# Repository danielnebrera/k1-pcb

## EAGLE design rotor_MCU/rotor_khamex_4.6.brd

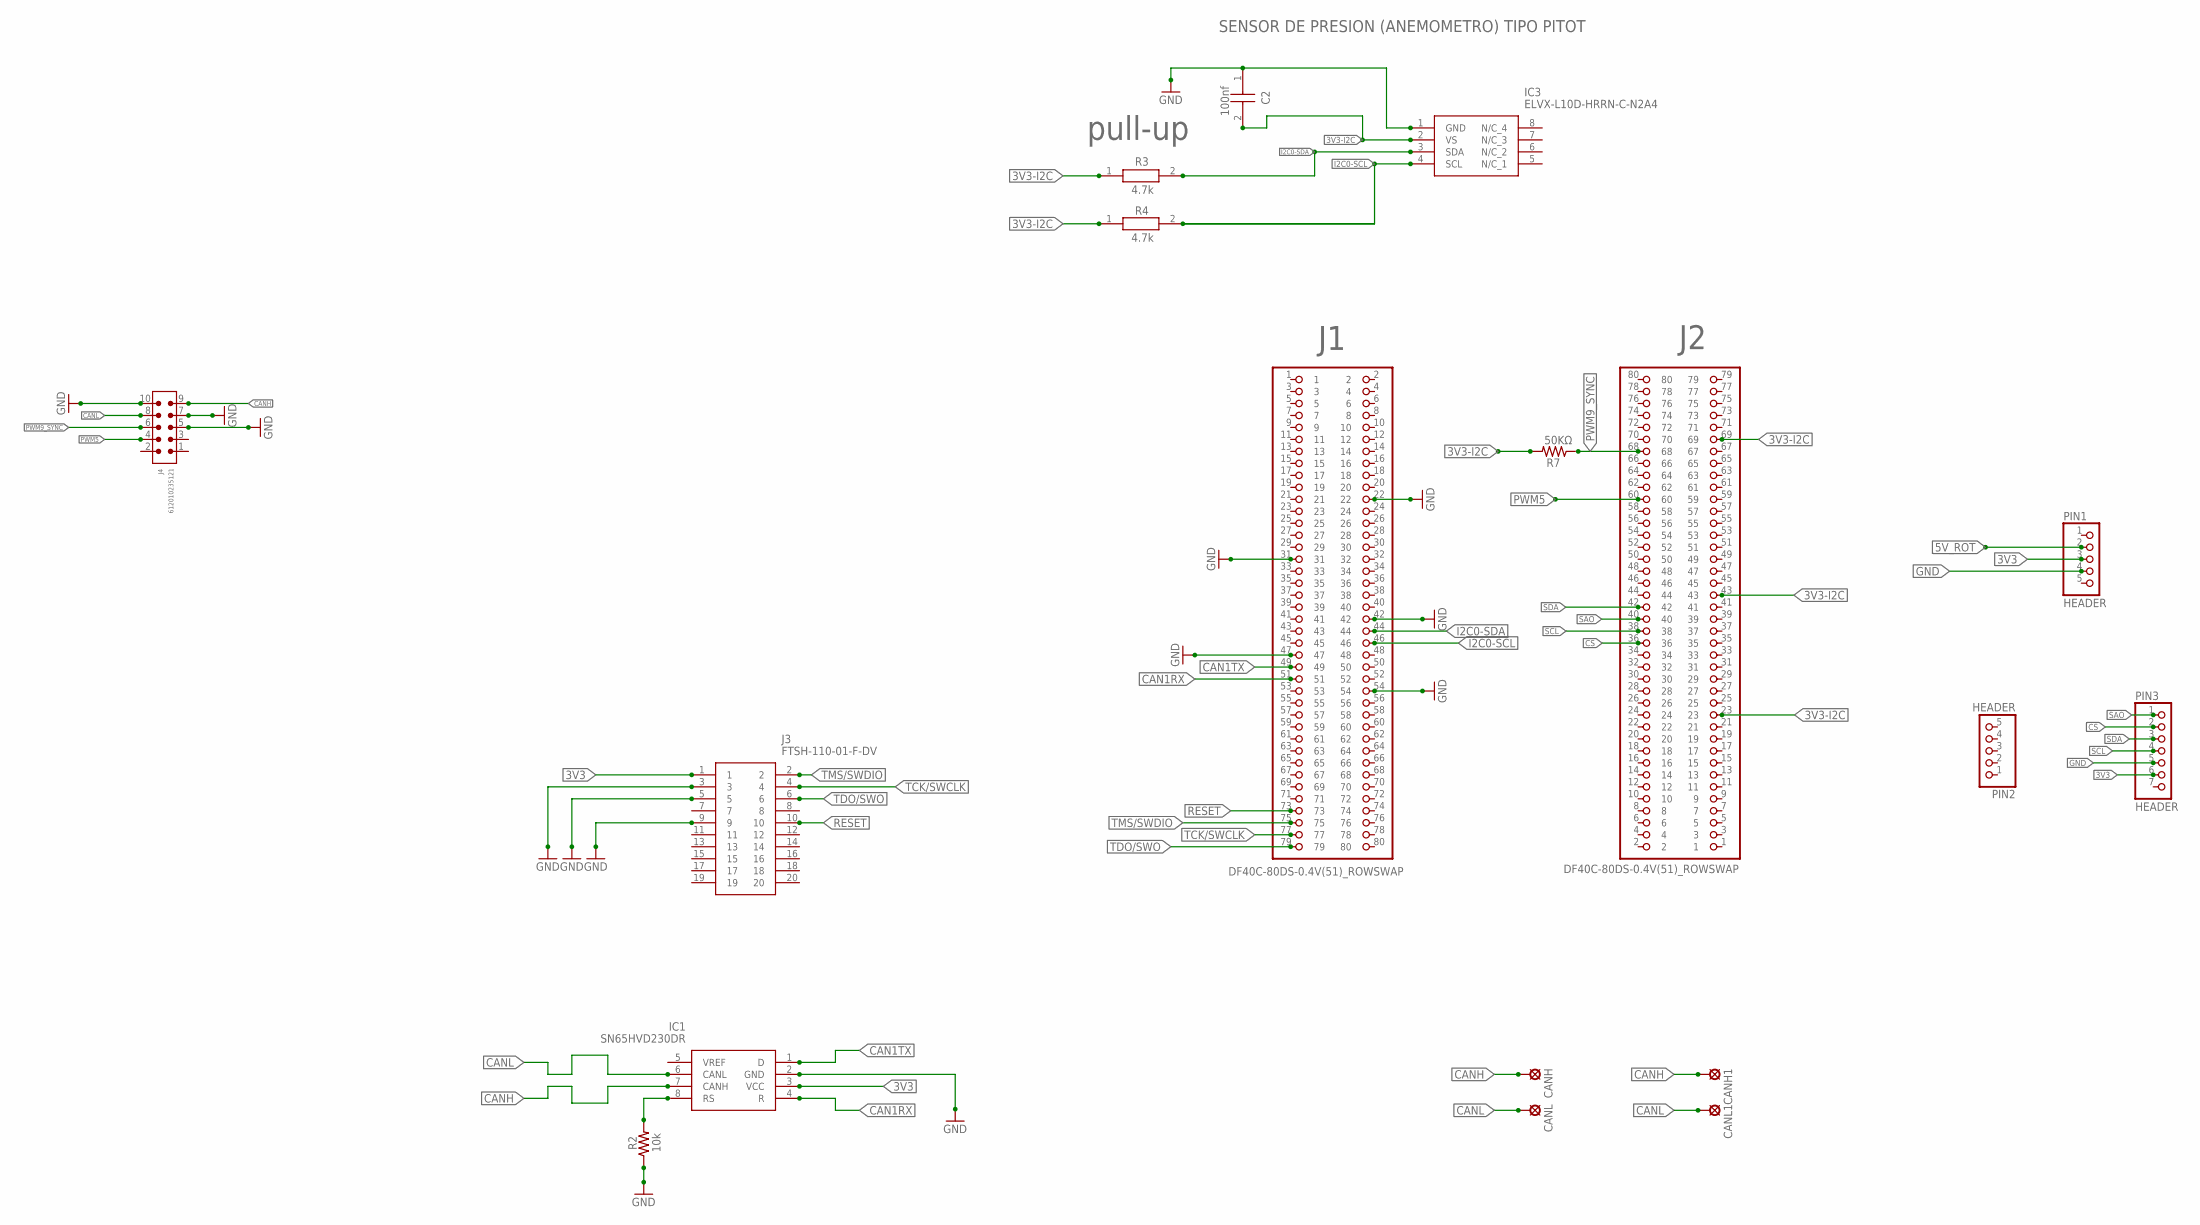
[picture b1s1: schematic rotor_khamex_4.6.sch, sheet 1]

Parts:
C2: 100nf; CAPC2012X145N
CANH, CANH1: LSP11
CANL, CANL1: LSP11
IC1: SN65HVD230DR; SOT127P600X175-8N
IC3: ELVX-L10D-HRRN-C-N2A4; ELVXL10DHRRNCN2A4
J1, J2: DF40C-80DS-0.4V(51)_ROWSWAP; HRS_DF40C-80DS-0.4V(51)_ROWSWAP
J3: FTSH-110-01-F-DV; FTSH-110-XX-YYY-DV
J4: 612010235121
PIN1, PIN2: HEADER; 1X05
PIN3: HEADER; 1X07
R2: 10k; M0805
R3, R4: 4.7k; RESC2012X50N
R7: 50KΩ; M0805

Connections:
3V3: IC1.3 (VCC), J3.1, PIN1.3, PIN3.6
3V3-I2C: C2.2, IC3.2 (VS), J2.23, J2.43, J2.69, R3.1, R4.1, R7.2
5V_ROT: PIN1.2; also elsewhere on the board
CAN1RX: IC1.4 (R), J1.51
CAN1TX: IC1.1 (D), J1.49
CANH: CANH.MP, CANH1.MP, IC1.7 (CANH), J4.9
CANL: CANL.MP, CANL1.MP, IC1.6 (CANL), J4.8
CS: J2.36, PIN3.2
GND: C2.1, IC1.2 (GND), IC3.1 (GND), J1.22, J1.31, J1.42, J1.47, J1.54, J3.3, J3.5, J3.9, J4.5, J4.7, J4.10, PIN1.4, PIN3.5, R2.1; also elsewhere on the board
I2C0-SCL: IC3.4 (SCL), J1.46, R4.2
I2C0-SDA: IC3.3 (SDA), J1.44, R3.2
unnamed: IC1.8 (RS), R2.2
PWM5: J2.60, J4.4
PWM9_SYNC: J2.68, J4.6, R7.1
RESET: J1.73, J3.10
SAO: J2.40, PIN3.1
SCL: J2.38, PIN3.4
SDA: J2.42, PIN3.3
TCK/SWCLK: J1.77, J3.4
TDO/SWO: J1.79, J3.6
TMS/SWDIO: J1.75, J3.2

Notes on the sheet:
SENSOR DE PRESION (ANEMOMETRO) TIPO PITOT
4.7k
pull-up

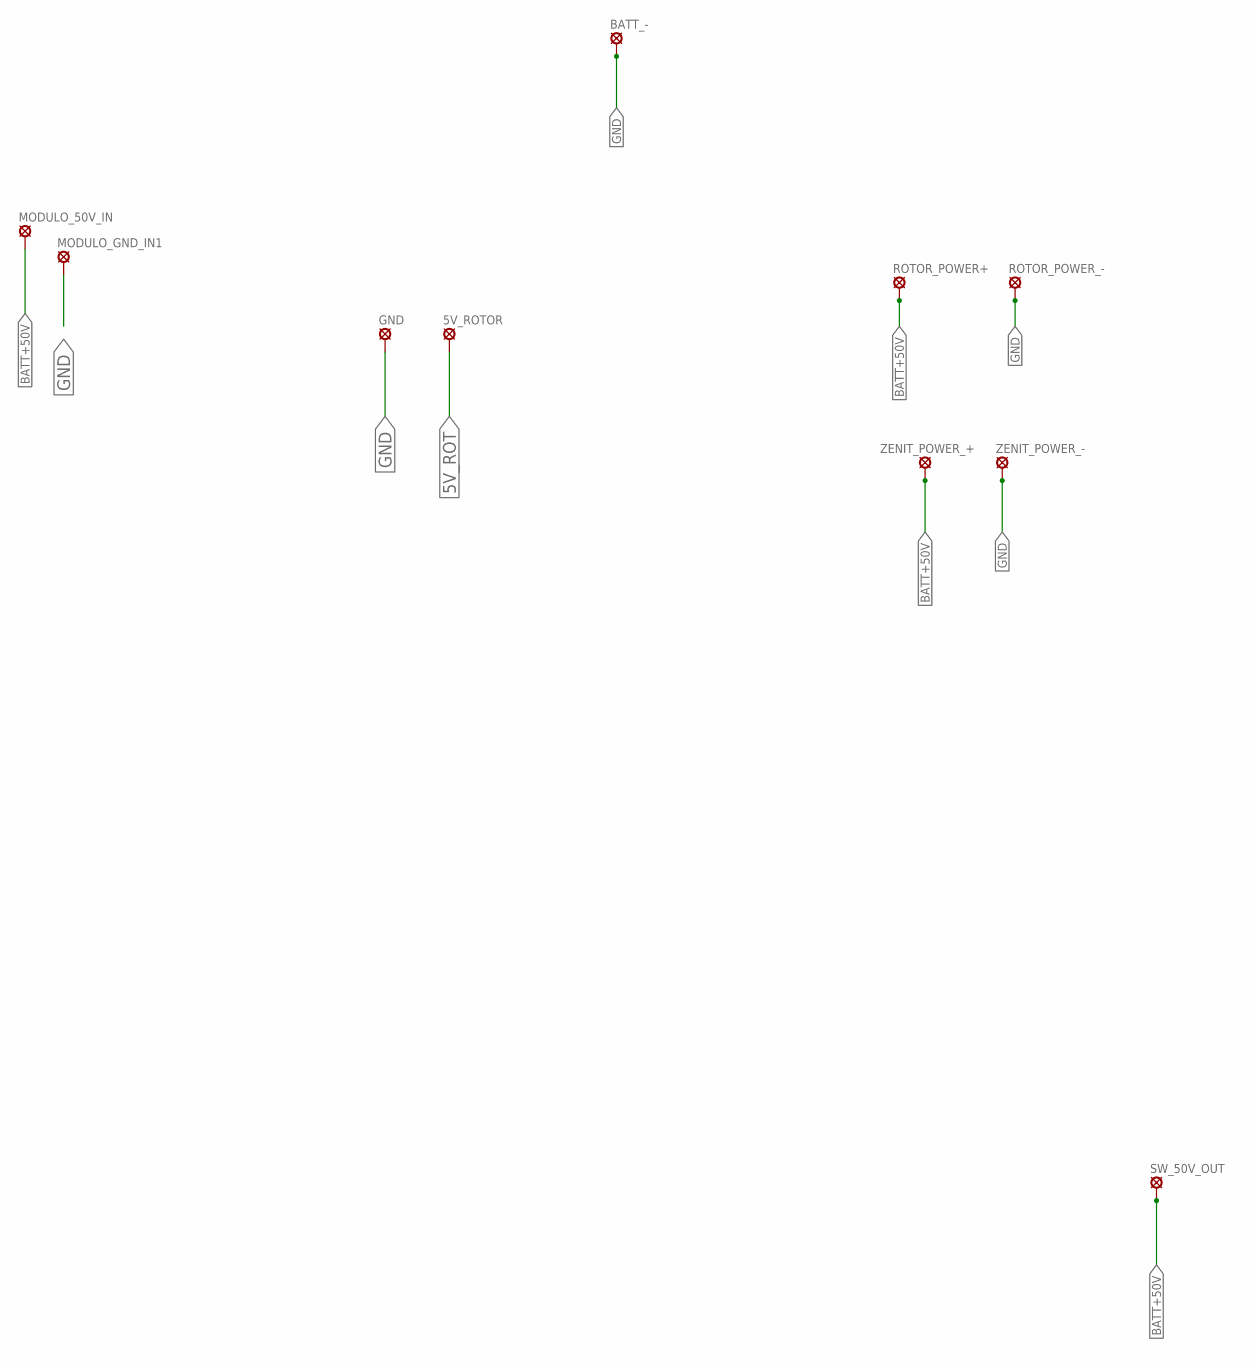
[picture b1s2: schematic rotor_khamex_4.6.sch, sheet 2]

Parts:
5V_ROTOR: SE14
BATT_-: SE14
GND: SE14
MODULO_50V_IN: SE14
MODULO_GND_IN1: SE14
ROTOR_POWER+: SE14
ROTOR_POWER_-: SE14
SW_50V_OUT: SE14
ZENIT_POWER_+: SE14
ZENIT_POWER_-: SE14

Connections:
5V_ROT: 5V_ROTOR.MP; also elsewhere on the board
BATT+50V: MODULO_50V_IN.MP, ROTOR_POWER+.MP, SW_50V_OUT.MP, ZENIT_POWER_+.MP
GND: BATT_-.MP, GND.MP, MODULO_GND_IN1.MP, ROTOR_POWER_-.MP, ZENIT_POWER_-.MP; also elsewhere on the board

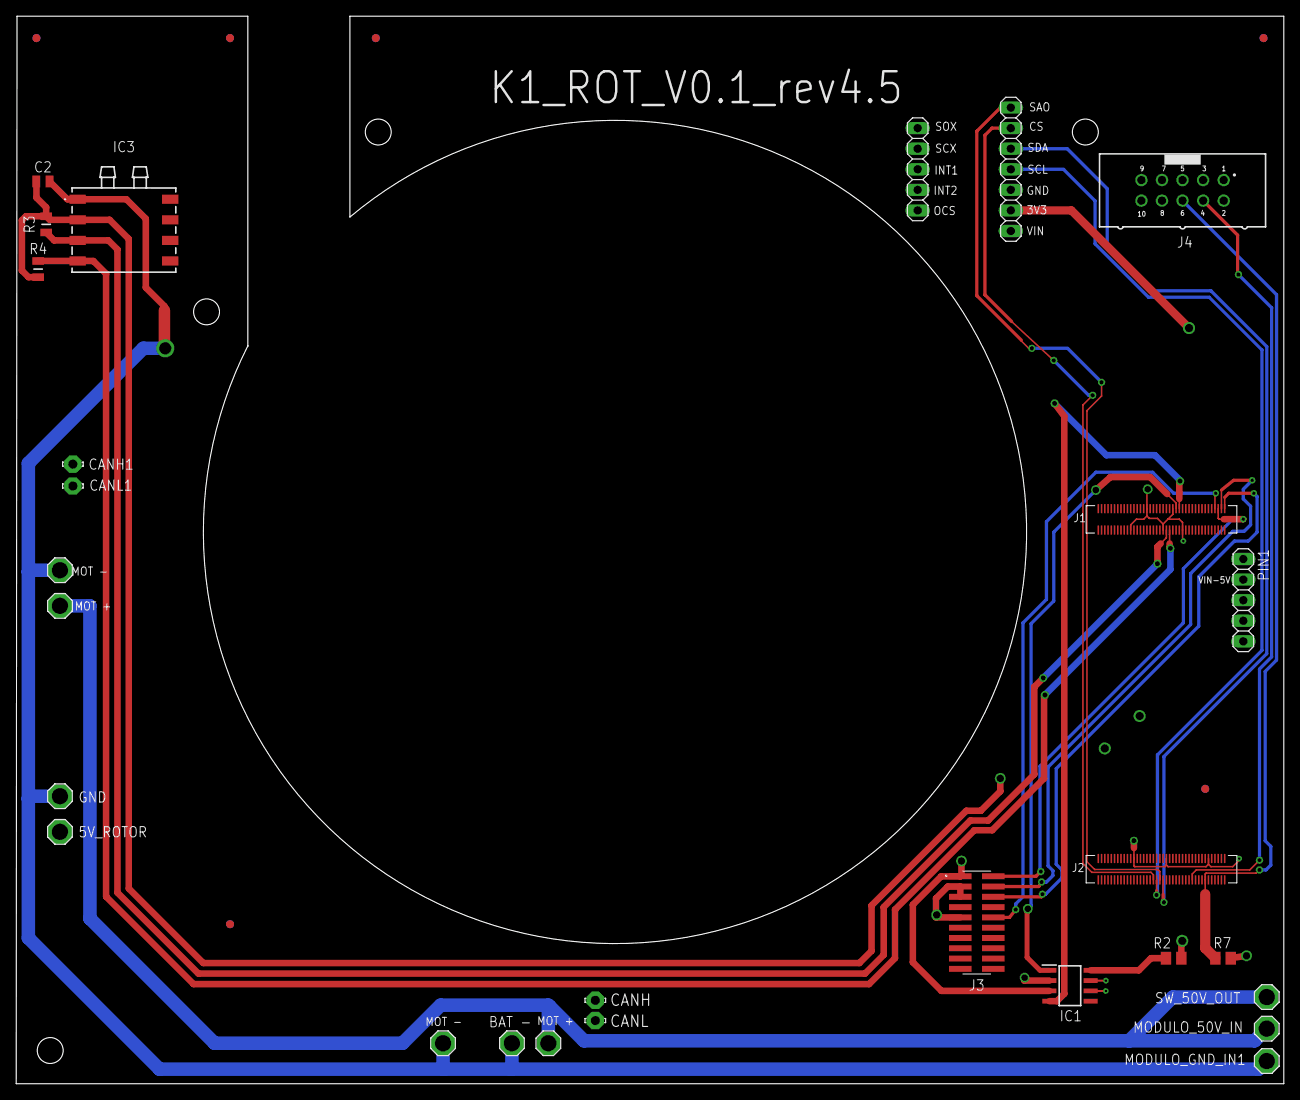
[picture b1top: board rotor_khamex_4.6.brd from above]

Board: 4 copper layers, 156.5 x 131.8 mm, 34 parts (0 on the bottom side), 22 nets.

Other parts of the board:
U$1, U$3, U$4, U$5, U$6, U$7: CIRCLE-1MM-3R

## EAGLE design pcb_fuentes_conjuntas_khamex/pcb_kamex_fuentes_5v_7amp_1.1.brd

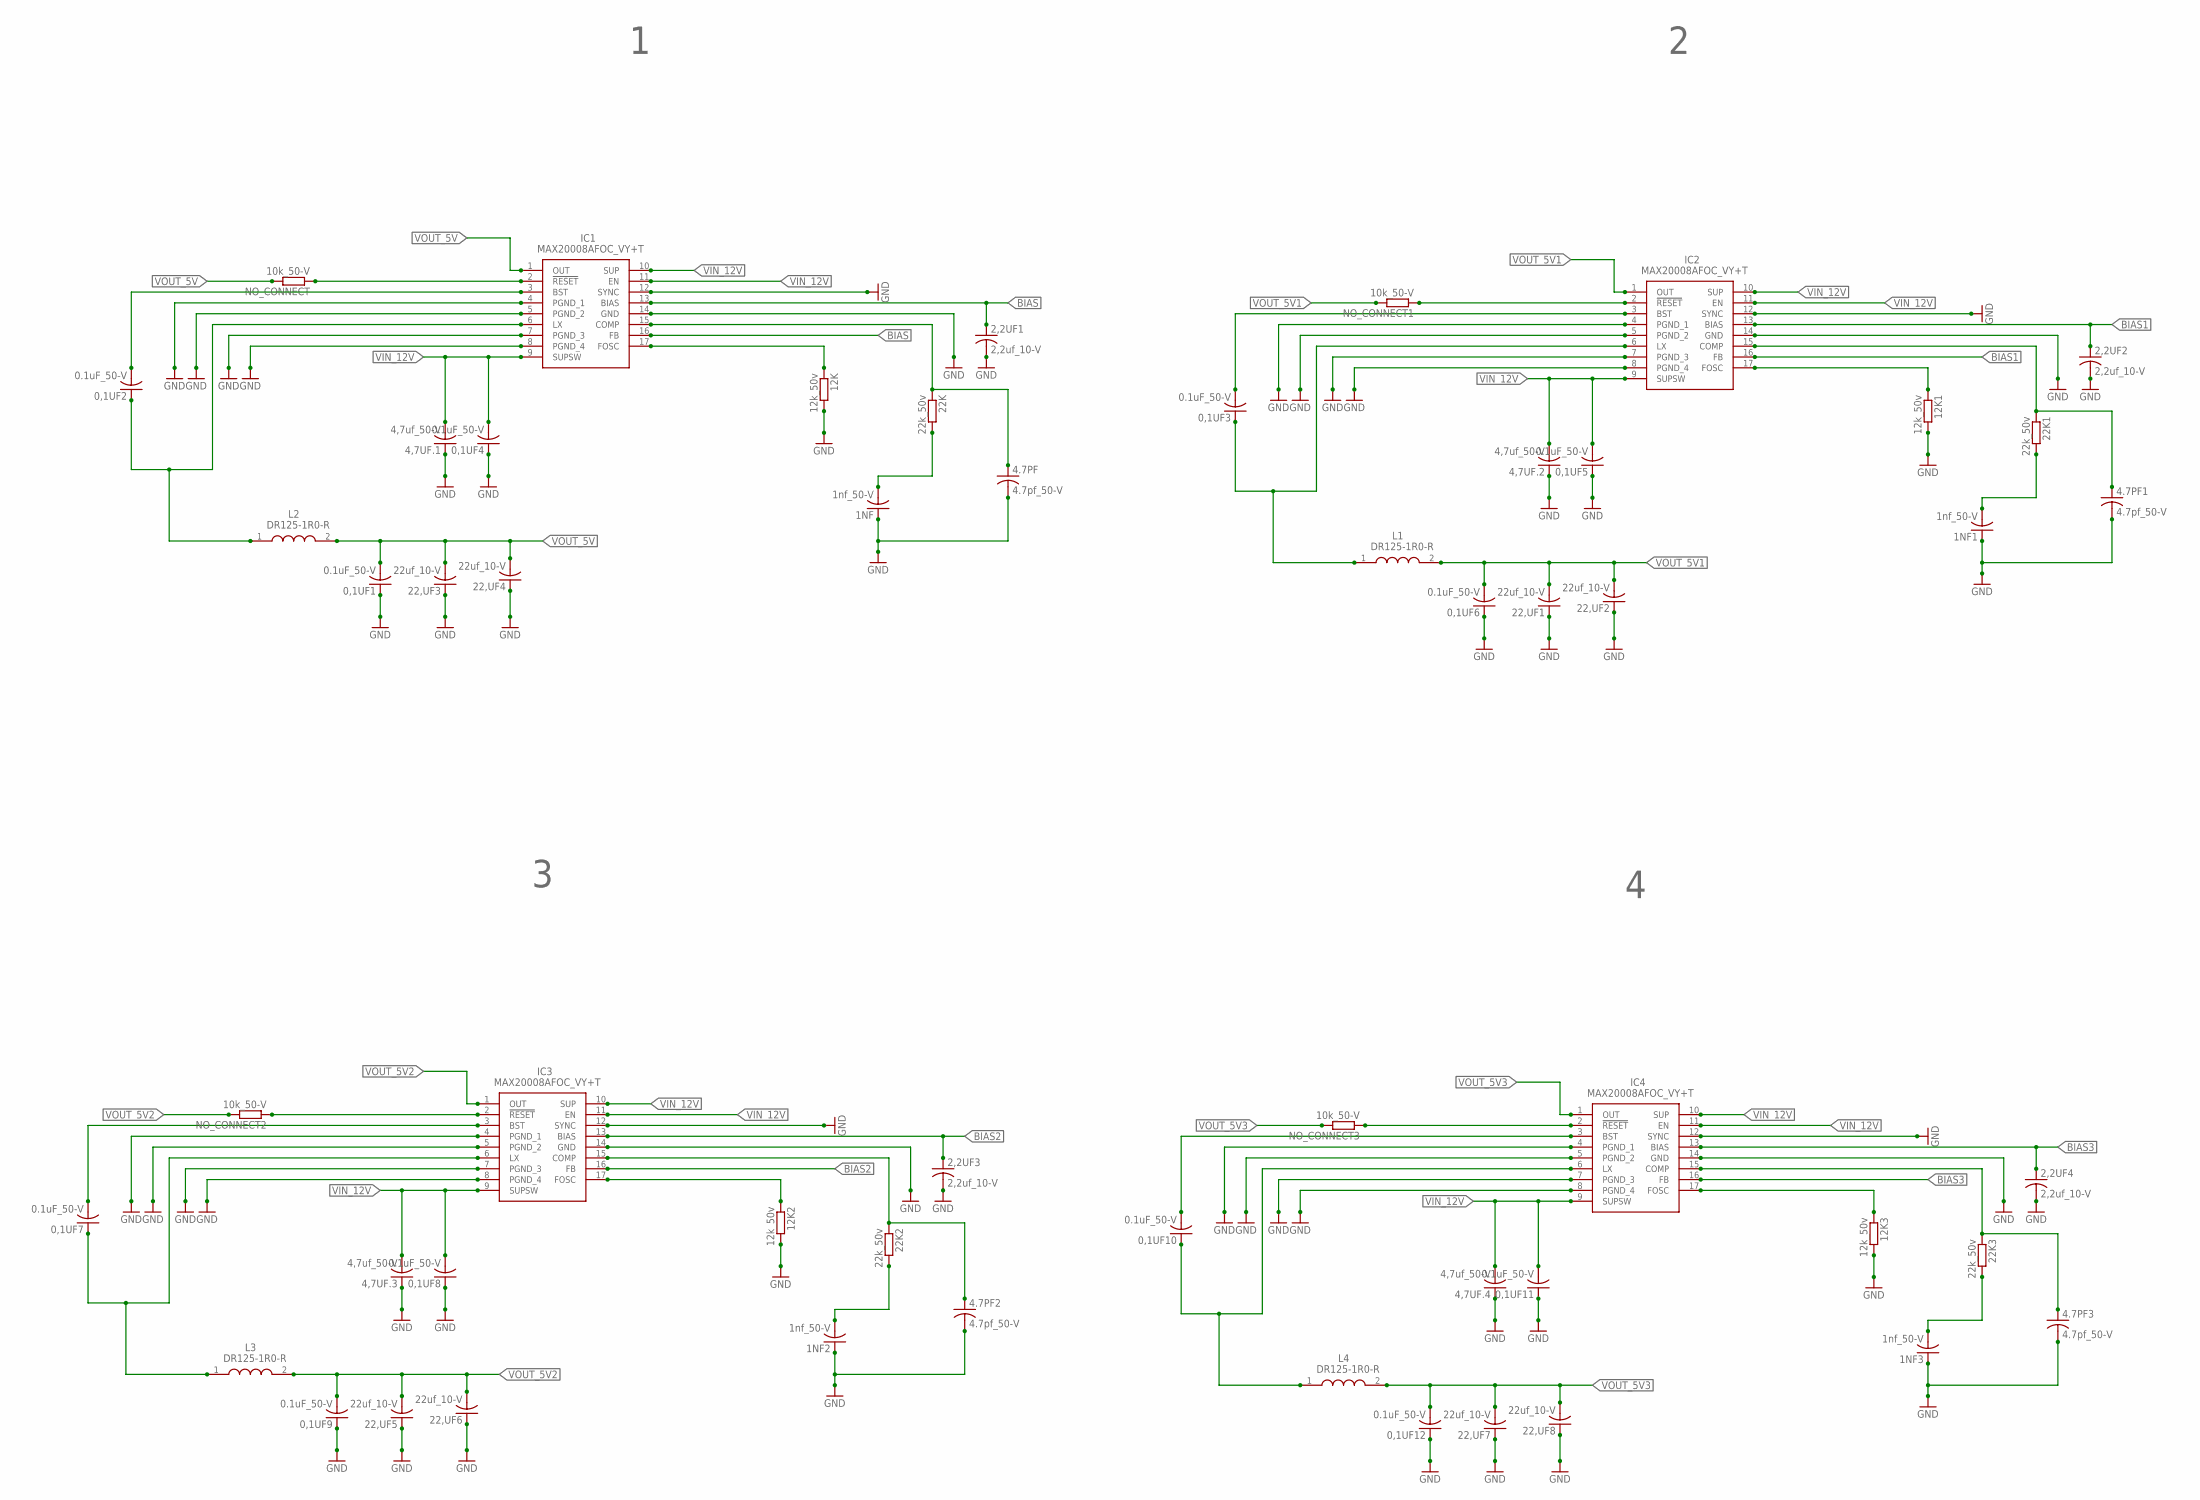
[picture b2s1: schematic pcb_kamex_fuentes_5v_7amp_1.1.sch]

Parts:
0,1UF1, 0,1UF2, 0,1UF3, 0,1UF4, 0,1UF5, 0,1UF6, 0,1UF7, 0,1UF8, 0,1UF9, 0,1UF10, 0,1UF11, 0,1UF12: 0.1uF_50-V; C0805
1NF, 1NF1, 1NF2, 1NF3: 1nf_50-V; C0805
2,2UF1, 2,2UF2, 2,2UF3, 2,2UF4: 2,2uf_10-V; C0805
4,7UF.1, 4,7UF.2, 4,7UF.3, 4,7UF.4: 4,7uf_50-V; C0805
4.7PF, 4.7PF1, 4.7PF2, 4.7PF3: 4.7pf_50-V; C0805
12K, 12K1, 12K2, 12K3: 12k_50v; M0805
22,UF1, 22,UF2, 22,UF3, 22,UF4, 22,UF5, 22,UF6, 22,UF7, 22,UF8: 22uf_10-V; C0805
22K, 22K1, 22K2, 22K3: 22k_50v; M0805
IC1, IC2, IC3, IC4: MAX20008AFOC_VY+T; MAX20008AFOCVYT
L1, L2, L3, L4: DR125-1R0-R; INDPM125125X600N
NO_CONNECT, NO_CONNECT1, NO_CONNECT2, NO_CONNECT3: 10k_50-V; M0805

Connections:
BIAS: 2,2UF1.1, IC1.13 (BIAS), IC1.16 (FB)
BIAS1: 2,2UF2.1, IC2.13 (BIAS), IC2.16 (FB)
BIAS2: 2,2UF3.1, IC3.13 (BIAS), IC3.16 (FB)
BIAS3: 2,2UF4.1, IC4.13 (BIAS), IC4.16 (FB)
BST: 0,1UF2.2, IC1.3 (BST)
BST1: 0,1UF3.2, IC2.3 (BST)
BST2: 0,1UF7.2, IC3.3 (BST)
BST3: 0,1UF10.2, IC4.3 (BST)
COM: 4.7PF.1, 22K.1, IC1.15 (COMP)
COM1: 4.7PF1.1, 22K1.1, IC2.15 (COMP)
COM2: 4.7PF2.1, 22K2.1, IC3.15 (COMP)
COM3: 4.7PF3.1, 22K3.1, IC4.15 (COMP)
GND: 0,1UF1.1, 0,1UF4.1, 0,1UF5.1, 0,1UF6.1, 0,1UF8.1, 0,1UF9.1, 0,1UF11.1, 0,1UF12.1, 1NF.1, 1NF1.1, 1NF2.1, 1NF3.1, 2,2UF1.2, 2,2UF2.2, 2,2UF3.2, 2,2UF4.2, 4,7UF.1.1, 4,7UF.2.1, 4,7UF.3.1, 4,7UF.4.1, 4.7PF.2, 4.7PF1.2, 4.7PF2.2, 4.7PF3.2, 12K.2, 12K1.2, 12K2.2, 12K3.2, 22,UF1.1, 22,UF2.1, 22,UF3.1, 22,UF4.1, 22,UF5.1, 22,UF6.1, 22,UF7.1, 22,UF8.1, IC1.4 (PGND_1), IC1.5 (PGND_2), IC1.7 (PGND_3), IC1.8 (PGND_4), IC1.12 (SYNC), IC1.14 (GND), IC2.4 (PGND_1), IC2.5 (PGND_2), IC2.7 (PGND_3), IC2.8 (PGND_4), IC2.12 (SYNC), IC2.14 (GND), IC3.4 (PGND_1), IC3.5 (PGND_2), IC3.7 (PGND_3), IC3.8 (PGND_4), IC3.12 (SYNC), IC3.14 (GND), IC4.4 (PGND_1), IC4.5 (PGND_2), IC4.7 (PGND_3), IC4.8 (PGND_4), IC4.12 (SYNC), IC4.14 (GND)
unnamed: 12K1.1, IC2.17 (FOSC)
unnamed: 1NF.2, 22K.2
unnamed: 0,1UF3.1, IC2.6 (LX), L1.1
unnamed: IC2.2 (!RESET), NO_CONNECT1.1
unnamed: 1NF1.2, 22K1.2
unnamed: 12K.1, IC1.17 (FOSC)
unnamed: 12K2.1, IC3.17 (FOSC)
unnamed: 0,1UF7.1, IC3.6 (LX), L3.1
unnamed: 0,1UF2.1, IC1.6 (LX), L2.1
unnamed: IC1.2 (!RESET), NO_CONNECT.1
unnamed: IC3.2 (!RESET), NO_CONNECT2.1
unnamed: 1NF2.2, 22K2.2
unnamed: 12K3.1, IC4.17 (FOSC)
unnamed: 0,1UF10.1, IC4.6 (LX), L4.1
unnamed: IC4.2 (!RESET), NO_CONNECT3.1
unnamed: 1NF3.2, 22K3.2
VIN_12V: 0,1UF4.2, 0,1UF5.2, 0,1UF8.2, 0,1UF11.2, 4,7UF.1.2, 4,7UF.2.2, 4,7UF.3.2, 4,7UF.4.2, IC1.9 (SUPSW), IC1.10 (SUP), IC1.11 (EN), IC2.9 (SUPSW), IC2.10 (SUP), IC2.11 (EN), IC3.9 (SUPSW), IC3.10 (SUP), IC3.11 (EN), IC4.9 (SUPSW), IC4.10 (SUP), IC4.11 (EN)
VOUT_5V: 0,1UF1.2, 22,UF3.2, 22,UF4.2, IC1.1 (OUT), L2.2, NO_CONNECT.2
VOUT_5V1: 0,1UF6.2, 22,UF1.2, 22,UF2.2, IC2.1 (OUT), L1.2, NO_CONNECT1.2
VOUT_5V2: 0,1UF9.2, 22,UF5.2, 22,UF6.2, IC3.1 (OUT), L3.2, NO_CONNECT2.2
VOUT_5V3: 0,1UF12.2, 22,UF7.2, 22,UF8.2, IC4.1 (OUT), L4.2, NO_CONNECT3.2

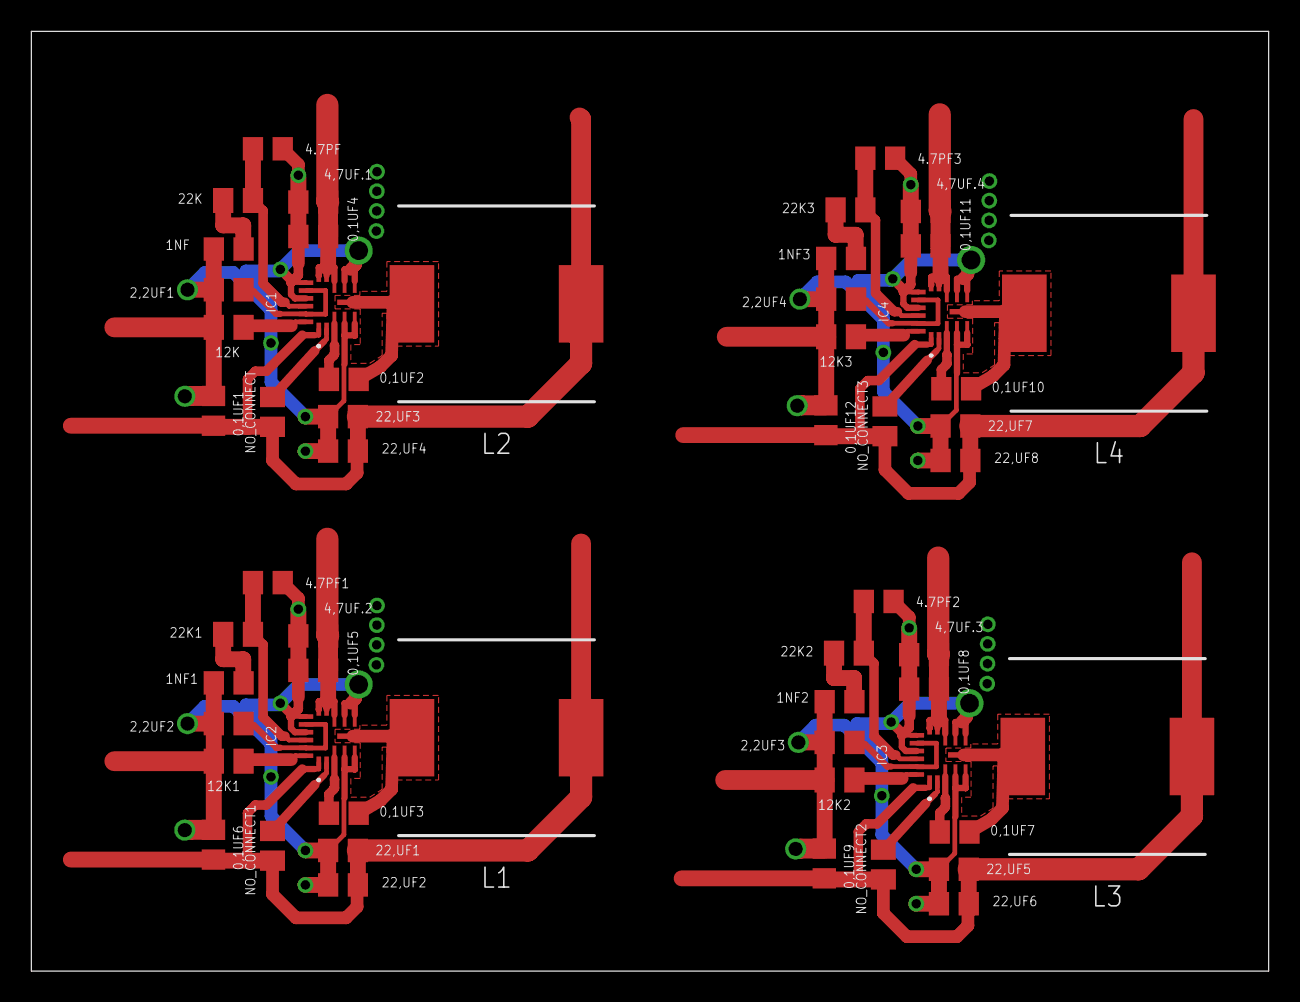
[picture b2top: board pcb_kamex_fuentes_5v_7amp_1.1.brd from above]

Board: 2 copper layers, 79.0 x 60.0 mm, 56 parts (0 on the bottom side), 34 nets.

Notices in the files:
parts and their libraries:
Eagle_WR-BHD_rev24a: Copyright: Würth Elektronik
